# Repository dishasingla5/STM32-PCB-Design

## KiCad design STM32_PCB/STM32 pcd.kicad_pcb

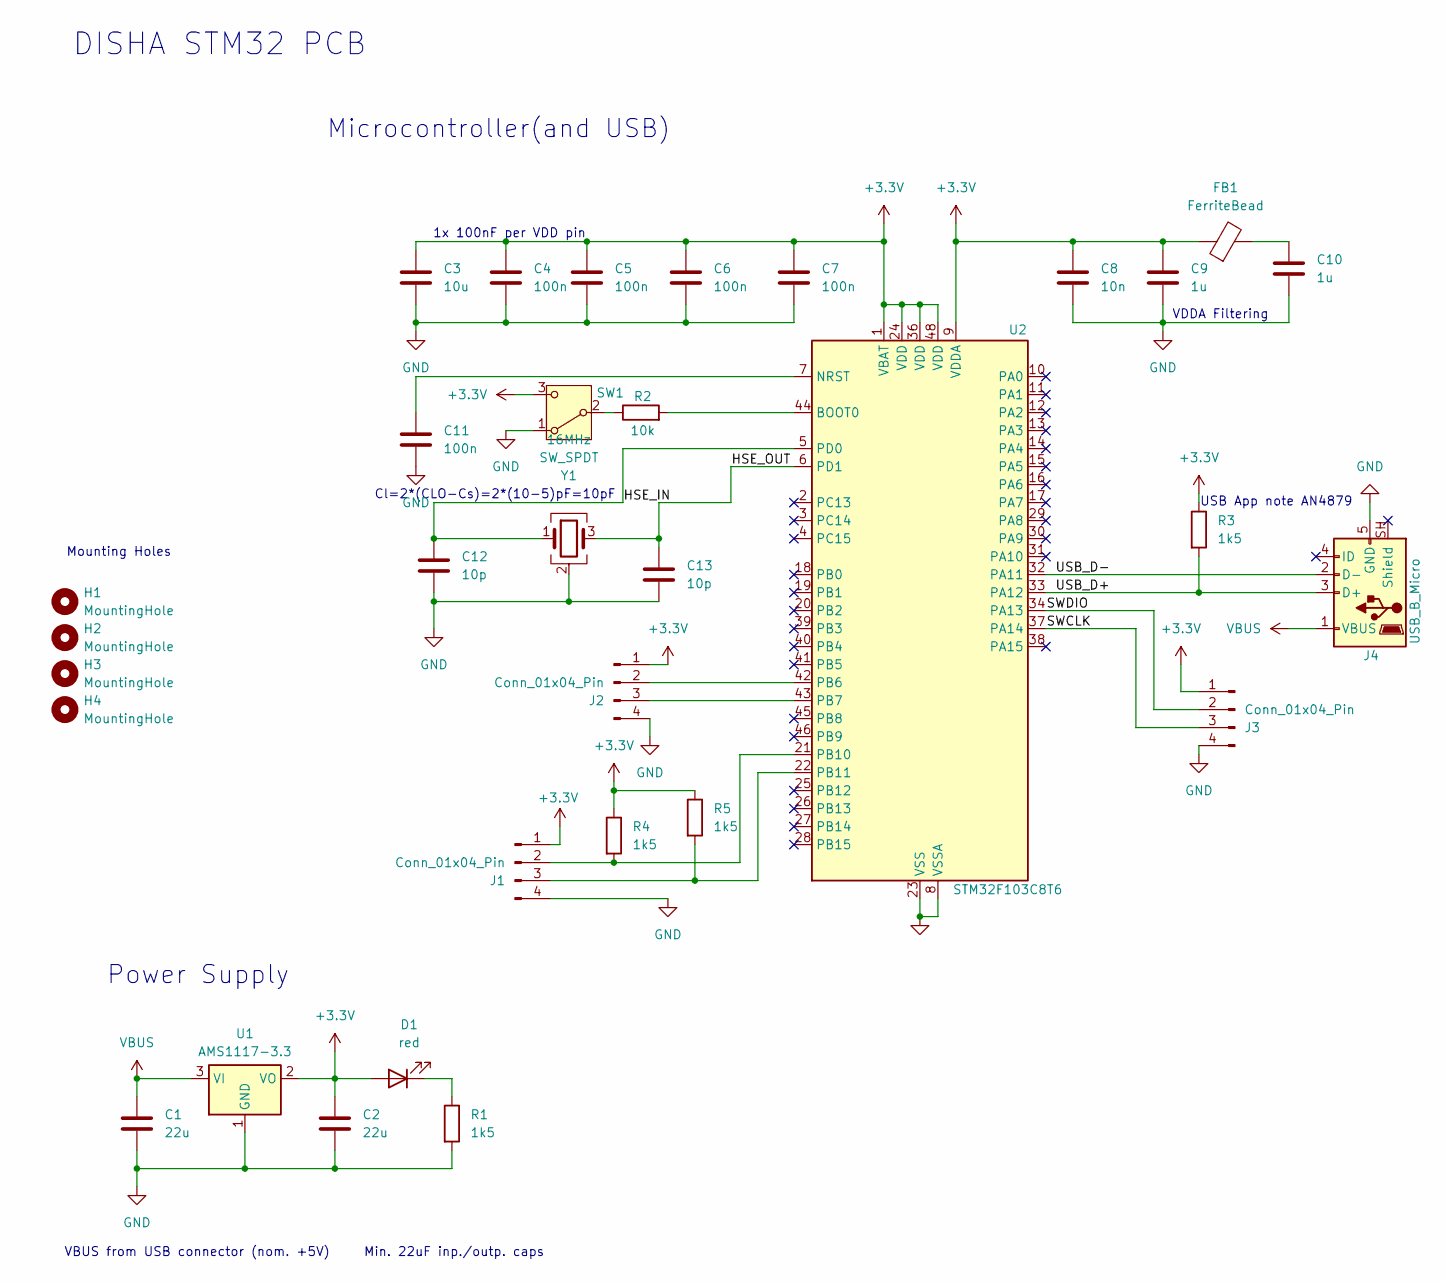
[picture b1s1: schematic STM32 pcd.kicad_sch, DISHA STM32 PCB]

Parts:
C1, C2: 22u; C_0805_2012Metric
C3: 10u; C_0603_1608Metric
C4, C5, C6, C7, C11: 100n; C_0402_1005Metric
C8: 10n; C_0402_1005Metric
C9, C10: 1u; C_0402_1005Metric
C12, C13: 10p; C_0402_1005Metric
D1: red; LED_0603_1608Metric
FB1: FerriteBead; L_0603_1608Metric
H1, H2, H3, H4: MountingHole; MountingHole_2.2mm_M2
J1, J2, J3: Conn_01x04_Pin; PinHeader_1x04_P2.54mm_Vertical_SMD_Pin1Right
J4: USB_B_Micro; USB_Micro-B_Wuerth_629105150521
R1, R3, R4, R5: 1k5; R_0402_1005Metric
R2: 10k; R_0402_1005Metric
SW1: SW_SPDT; SW_SPDT_PCM12
U1: AMS1117-3.3; SOT-223-3_TabPin2
U2: STM32F103C8T6; LQFP-48_7x7mm_P0.5mm
Y1: 16MHz; Crystal_SMD_3225-4Pin_3.2x2.5mm

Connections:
+3.3V: C2.1, C3.1, C4.1, C5.1, C6.1, C7.1, C8.1, C9.1, D1.2 (A), FB1.1, J1.1, J2.1, J3.1, R3.1, R4.1, R5.1, SW1.3 (C), U1.2 (VO), U2.1 (VBAT), U2.9 (VDDA), U2.24 (VDD), U2.36 (VDD), U2.48 (VDD)
/HSE_IN: C12.1, U2.5 (PD0), Y1.1
/HSE_OUT: C13.1, U2.6 (PD1), Y1.3
/SWCLK: J3.3, U2.37 (PA14)
/SWDIO: J3.2, U2.34 (PA13)
/USB_D+: J4.3 (D+), R3.2, U2.33 (PA12)
/USB_D-: J4.2 (D-), U2.32 (PA11)
GND: C1.2, C2.2, C3.2, C4.2, C5.2, C6.2, C7.2, C8.2, C9.2, C10.2, C11.2, C12.2, C13.2, J1.4, J2.4, J3.4, J4.5 (GND), R1.2, SW1.1 (A), U1.1 (GND), U2.8 (VSSA), U2.23 (VSS), U2.35 (VSS), U2.47 (VSS), Y1.2 (G), Y1.4 (G)
unnamed: C10.1, FB1.2
unnamed: D1.1 (K), R1.1
unnamed: J1.2, R4.2, U2.21 (PB10)
unnamed: J1.3, R5.2, U2.22 (PB11)
unnamed: J2.2, U2.42 (PB6)
unnamed: J2.3, U2.43 (PB7)
unnamed: R2.1, SW1.2 (B)
unnamed: R2.2, U2.44 (BOOT0)
unnamed: C11.1, U2.7 (NRST)
VBUS: C1.1, J4.1 (VBUS), U1.3 (VI)

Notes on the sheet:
VDDA Filtering
DISHA STM32 PCB
Power Supply
Mounting Holes
1x 100nF per VDD pin
Cl=2*(CLO-Cs)=2*(10-5)pF=10pF
USB App note AN4879
VBUS from USB connector (nom. +5V) Min. 22uF inp./outp. caps
Microcontroller(and USB)

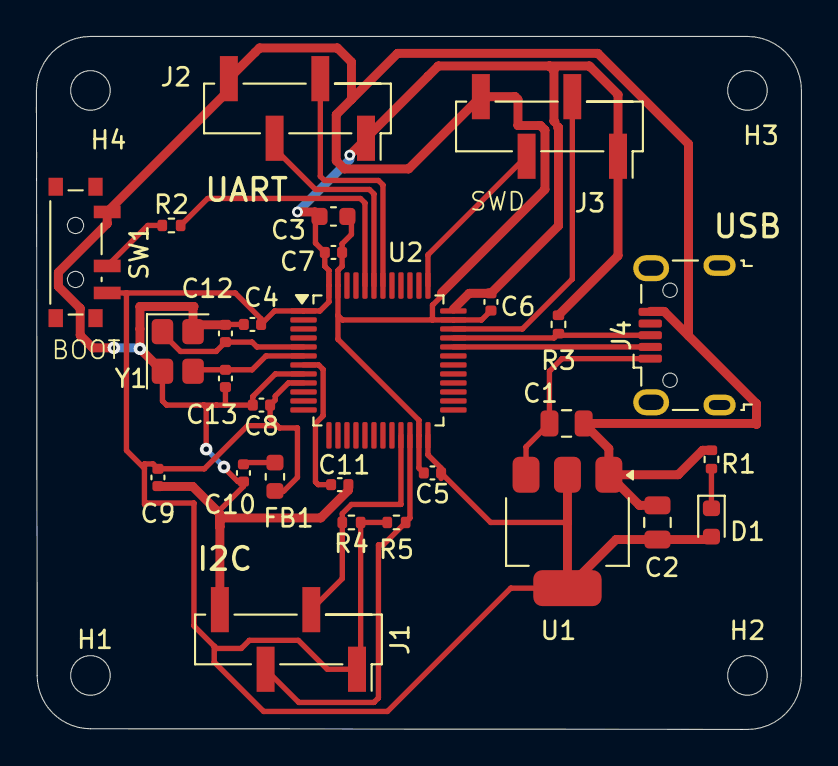
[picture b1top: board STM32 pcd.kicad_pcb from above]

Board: 2 copper layers, 42.5 x 38.5 mm, 32 parts (0 on the bottom side), 18 nets.
